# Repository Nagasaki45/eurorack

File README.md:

# Some eurorack modules

I'm trying. Let's see where it goes.

# Modules

- [1 2 3](<1 2 3/README.md>) - 8 steps resettable sequencial clock
- [I M smart](<I M smart/README.md>) - Utility mixer with some nice extras
- [let's play together](<lets play together/README.md>) - Analog + MIDI clock source

## Resources

- [Music Thing Modular parts library](https://github.com/TomWhitwell/MTM-Parts-Library).

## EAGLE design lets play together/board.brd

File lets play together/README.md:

# let's play together

## Analog + MIDI clock source in 4 hp

A clock module to sync your eurorack and external MIDI gear. The analog clock at the `CLK` output always ticks and the MIDI clock has a switch to start and stop that send the appropriate MIDI messages when flicked either side. There's a jumper at the back to send the analog clock to the gate bus, if you want to minimise cables to your other clocked modules.

### Summary of features

- Analog + MIDI clock
- MIDI start and stop toggle
- Can be set to output analog clock to gate bus via jumper
- Arduino based, so can be hacked (to change analog PPQN, tempo range, start and stop toggle functionality, etc.)
- MIDI clock output switchable between MIDI TRS type A and type B at with a switch at the back

## Specs

- Width: 4hp
- Depth: 29mm
- Power: 29mA @ 12V / <1mA @ -12V

## Build notes

- The LED orientation is not marked on the PCB. The longer (positive) leg should be closer to the edge of the board.
- I use an unbranded arduino pro mini 5V 16MHz ATMega328. A pro micro should also work. It's slightly more expensive, but is simpler to work with due to onboard USB connection.
- The arduino sketch depends on the [midilab's uClock](https://github.com/midilab/uClock) library. Make sure to install it first.

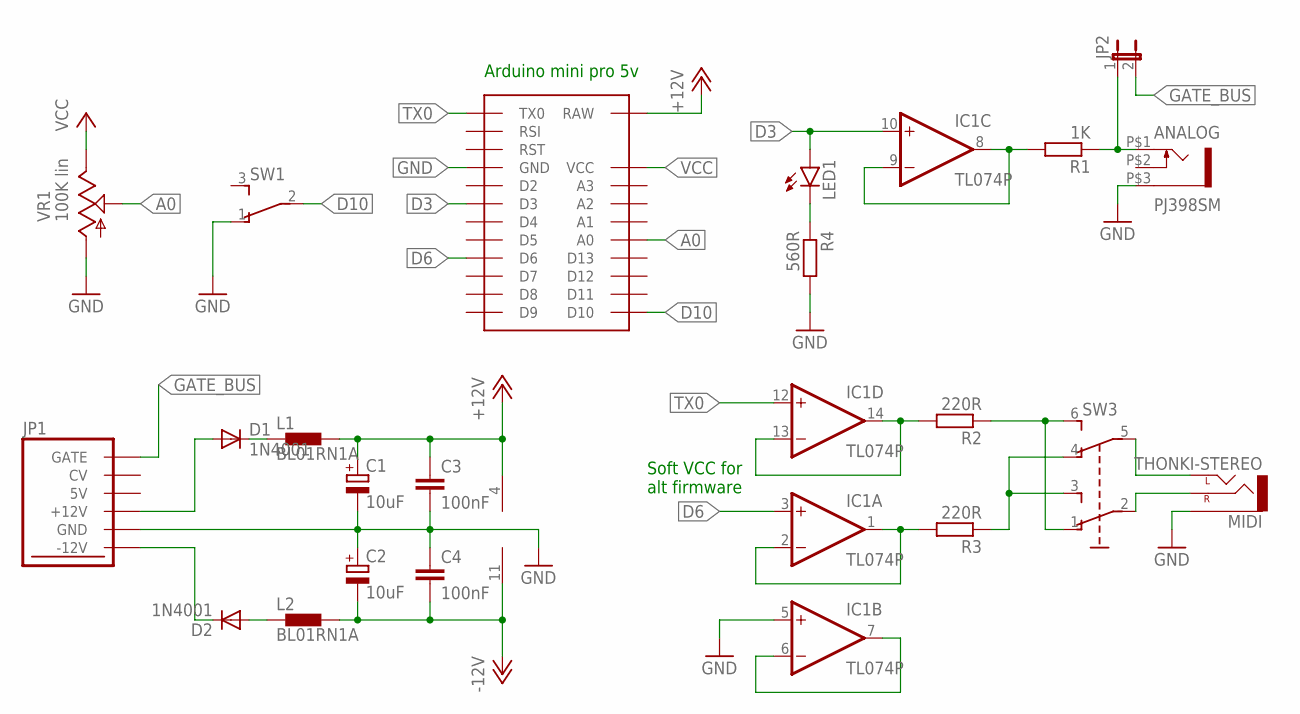
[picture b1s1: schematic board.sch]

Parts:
ANALOG: PJ398SM; WQP-PJ301M-12_JACK
C1, C2: 10uF; E2,5-6E; MPN UVR2A100MED1TD
C3, C4: 100nF; C025-024X044; MPN MC0805Y104M500A2.54MM
D1, D2: 1N4001; DO41-10; MPN 1N4001-E3/54
IC1: TL074P; DIL14; MPN TL074BCN
JP1: EUROPOWER16
JP2: JP1E; JP1; MPN 826926-2
JP3: ARDUINO_PRO_MINI_SOCKET
L1, L2: BL01RN1A; MPN BL01RN1A1D2B
LED1: LED3MM; MPN HLMP-1700
MIDI: THONKI-STEREO; WQP-PJ366ST_JACK
R1: 1K; 0204/5; MPN LR0204F1K0
R2, R3: 220R; 0204/5; MPN LR0204F100K
R4: 560R; 0204/5; MPN LR0204F100K
SW1: SUB-MINI; TL3XPO
SW3: JS202011CQN; MPN JS202011CQN
VR1: 100K lin; 9MM_SNAP-IN_POT

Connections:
+12V: C1.+, C3.1, IC1.4 (V+), JP3.1 (RAW), L1.2
-12V: C2.-, C4.2, IC1.11 (V-), L2.2
A0: JP3.8 (A0), VR1.2 (S)
CLOCK: ANALOG.P$1 (2), JP2.1, R1.1
D3: IC1.10 (+IN), JP3.18 (D3), LED1.A
D6: IC1.3 (+IN), JP3.21 (D6)
D10: JP3.12 (D10), SW1.2
GATE_BUS: JP1.15 (GATE), JP1.16 (GATE), JP2.2
GND: ANALOG.P$3 (1), C1.-, C2.+, C3.2, C4.1, IC1.5 (+IN), JP1.3 (GND), JP1.4 (GND), JP1.5 (GND), JP1.6 (GND), JP1.7 (GND), JP1.8 (GND), JP3.2 (GND), JP3.16 (GND), MIDI.P$3_SLEEVE (SLEEVE), R4.2, SW1.1 (O), VR1.1 (A)
unnamed: D1.A, JP1.9 (+12V), JP1.10 (+12V)
unnamed: D2.C, JP1.1 (-12V), JP1.2 (-12V)
unnamed: D1.C, L1.1
unnamed: D2.A, L2.1
unnamed: IC1.1 (OUT), IC1.2 (-IN), R3.2
unnamed: R2.1, SW3.1 (A1), SW3.6 (B2)
unnamed: IC1.13 (-IN), IC1.14 (OUT), R2.2
unnamed: LED1.K (C), R4.1
unnamed: MIDI.P$1_TIP (LEFT), SW3.5 (COM2)
unnamed: MIDI.P$2_SWITCH (RIGHT), SW3.2 (COM1)
unnamed: R3.1, SW3.3 (B1), SW3.4 (A2)
unnamed: IC1.6 (-IN), IC1.7 (OUT)
unnamed: IC1.8 (OUT), IC1.9 (-IN), R1.2
TX0: IC1.12 (+IN), JP3.13 (TX0)
VCC: JP3.4 (VCC), VR1.3 (E)

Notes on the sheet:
Arduino mini pro 5v
Soft VCC for alt firmware

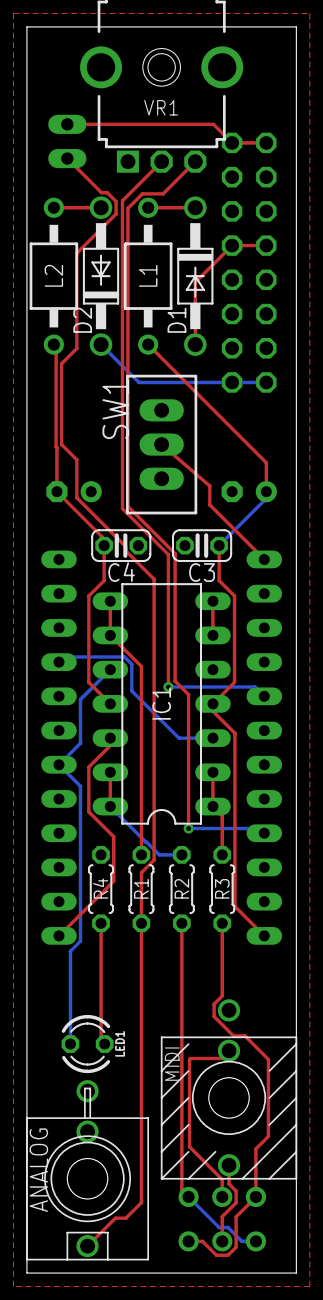
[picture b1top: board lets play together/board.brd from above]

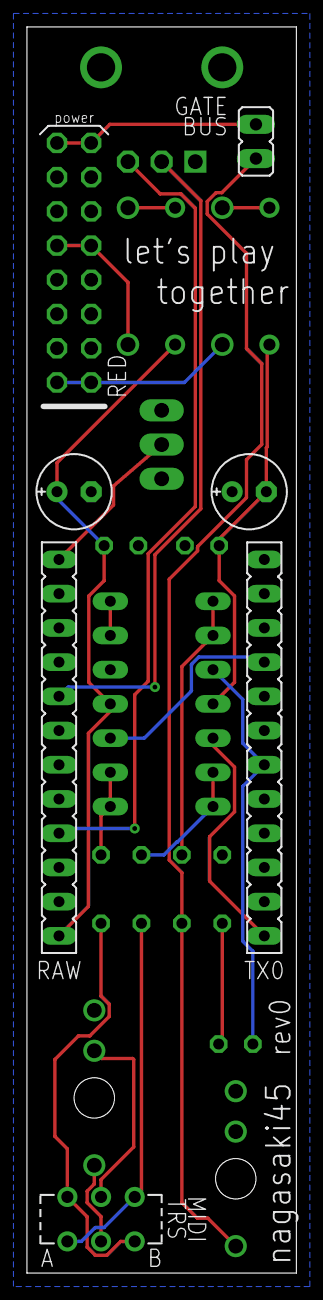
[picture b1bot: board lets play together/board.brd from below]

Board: 2 copper layers, 20.0 x 92.5 mm, 22 parts (6 on the bottom side), 24 nets.

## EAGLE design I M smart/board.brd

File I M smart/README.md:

# I M smart

## Utility mixer with some nice extras in 4 hp

At its basis this module is a 3 channels mixer, but with extra features down its sleeve! The first two channels have dedicated outputs. Connecting a patch cable to these outputs takes channel 1 or 2 out of the mix. Input 1 is normalised to ~+6 volts, so without anything plugged into input 1 the first knob can add positive voltages to the mix or to the dedicated output. Similarly, channel 2 is normalised to ~-6 volts, to add some negative voltages to the mix or to output 2. Channel 3's knob is an attenuverter. This channel is not normalised to anything, because normalised attenuverters are super annoying to set to 0. Lastly, there's only one PCB behind the panel, and a quite low components count, making it relatively cheap and easy build.

### Summary of features

- 3 channels mixer
- 2 attenuators
- 1 attenuverter
- Positive and negative manual voltages

## Specs

- Width: 4hp
- Depth: 25mm
- Power: 5mA @ 12V / 5mA @ -12V

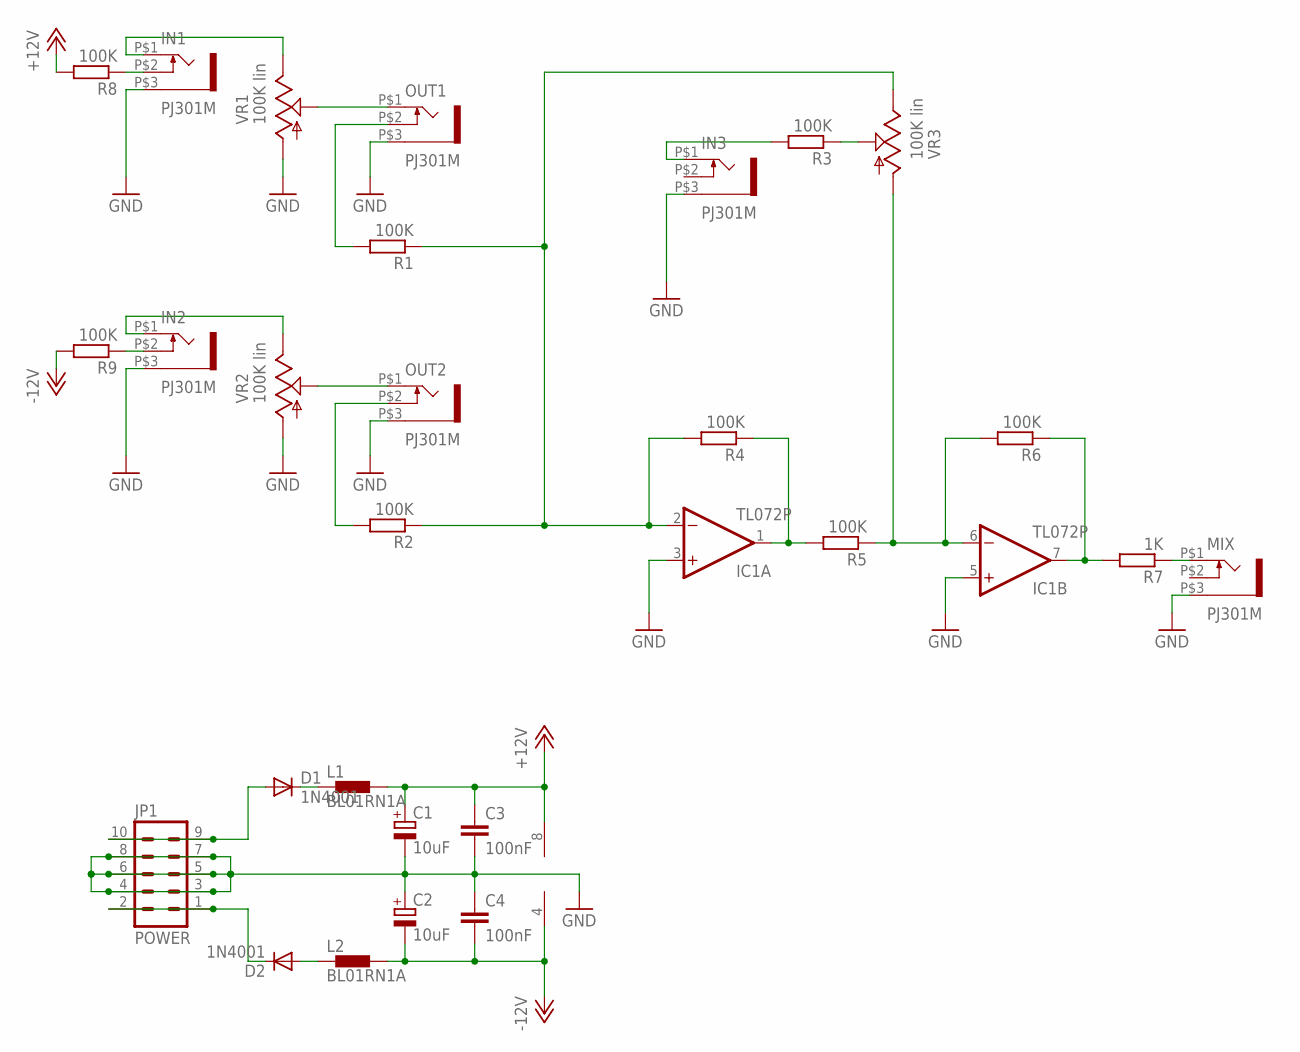
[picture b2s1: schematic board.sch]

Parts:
C1, C2: 10uF; E2,5-6E; MPN UVR2A100MED1TD
C3, C4: 100nF; C025-024X044; MPN MC0805Y104M500A2.54MM
D1, D2: 1N4001; DO41-10; MPN 1N4001-E3/54
IC1: TL072P; DIL08; MPN TL072IP
IN1, IN2, IN3: PJ301M; WQP-PJ301M-12_JACK
JP1: POWER; EURO_PWR_HEADER_FAT; MPN 2213S-10G
L1, L2: BL01RN1A; MPN BL01RN1A1D2B
MIX: PJ301M; WQP-PJ301M-12_JACK
OUT1, OUT2: PJ301M; WQP-PJ301M-12_JACK
R1, R2, R3, R4, R5, R6, R8, R9: 100K; 0204/5; MPN LR0204F100K
R7: 1K; 0204/5; MPN LR0204F1K0
VR1, VR2, VR3: 100K lin; 9MM_SNAP-IN_POT

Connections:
+12V: C1.+, C3.1, IC1.8 (V+), L1.2, R8.2
-12V: C2.-, C4.2, IC1.4 (V-), L2.2, R9.2
GND: C1.-, C2.+, C3.2, C4.1, IC1.3 (+IN), IC1.5 (+IN), IN1.P$3 (1), IN2.P$3 (1), IN3.P$3 (1), JP1.3, JP1.4, JP1.5, JP1.6, JP1.7, JP1.8, MIX.P$3 (1), OUT1.P$3 (1), OUT2.P$3 (1), VR1.1 (A), VR2.1 (A)
MIX+: MIX.P$1 (2), R7.1
MIXER: IC1.2 (-IN), R1.1, R2.1, R4.2, VR3.3 (E)
unnamed: D1.A, JP1.9, JP1.10
unnamed: D2.C, JP1.1, JP1.2
unnamed: D1.C, L1.1
unnamed: D2.A, L2.1
unnamed: IN1.P$1 (2), VR1.3 (E)
unnamed: IN2.P$1 (2), VR2.3 (E)
unnamed: OUT1.P$1 (2), VR1.2 (S)
unnamed: OUT2.P$1 (2), VR2.2 (S)
unnamed: IN3.P$1 (2), R3.2
unnamed: R3.1, VR3.2 (S)
unnamed: IN2.P$2 (3), R9.1
unnamed: IN1.P$2 (3), R8.1
unnamed: OUT1.P$2 (3), R1.2
unnamed: OUT2.P$2 (3), R2.2
unnamed: IC1.1 (OUT), R4.1, R5.2
unnamed: IC1.6 (-IN), R5.1, R6.2, VR3.1 (A)
unnamed: IC1.7 (OUT), R6.1, R7.2

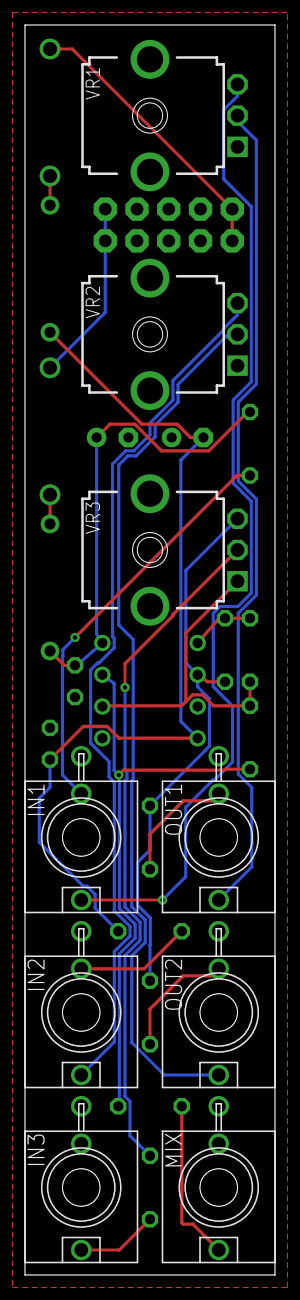
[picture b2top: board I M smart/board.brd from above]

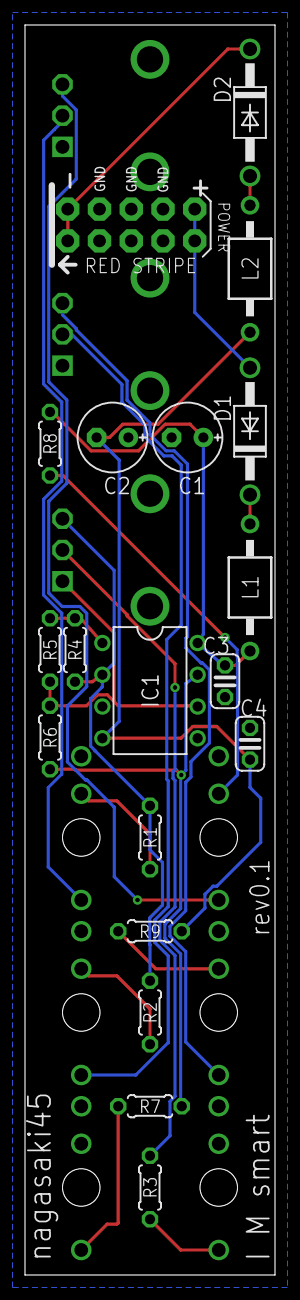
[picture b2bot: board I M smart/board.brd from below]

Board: 2 copper layers, 20.0 x 100.0 mm, 28 parts (19 on the bottom side), 22 nets.

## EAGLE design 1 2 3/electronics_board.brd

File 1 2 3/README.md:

# 1 2 3

## 8 steps resettable sequencial clock in 4 hp

With a clock going into the CLK input output 1 to 8 will go high one at a time. A reset input or a button can reset the sequence back to the 1st step. The outputs are designed to be mixed with simple passive multiples. No need for additional OR logic / gate combiner. For example, try to connect output 1 and 3 to a passive multiple or stackable and also to a kick drum trigger input, and output 5 and 8 in a similar fashion to a snare trigger input. Got the idea? The module can also work in audio rate to produce various sub-octaves and sync effects.

## Specs

- Width: 4hp
- Depth: 44mm
- Power: 29mA @ 12V / 16mA @ -12V

## Useful references

- [Ken Stone's gate sequencer](https://www.elby-designs.com/webtek/cgs/cgs89/cgs89_gate_sequencer.html)
- [Ken Stone's gate to trigger](https://www.muffwiggler.com/forum/viewtopic.php?t=46926)
- [Passive OR logic](https://forum.aemodular.com/thread/365/diy-project-02-passive-logic)
- [Non inverting transistor switch](http://www.timstinchcombe.co.uk/index.php?pge=a161)
- [4022 datasheet](https://www.ti.com/lit/ds/symlink/cd4022b.pdf)
- [Reset input simulation](http://www.falstad.com/circuit/circuitjs.html?cct=$+0+0.000005+0.9487735836358526+50+5+43%0Ar+96+240+96+288+0+100000%0Ar+240+240+240+288+0+100000%0Ag+240+304+240+320+0%0Ag+304+304+304+320+0%0AR+304+96+304+64+0+0+40+12+0+0+0.5%0At+272+224+304+224+0+1+-9.770126409985263+0.5279543655005605+100%0Ar+304+96+304+144+0+10000%0Ar+336+192+400+192+0+100000%0Ag+432+304+432+320+0%0AR+432+96+432+64+0+0+40+12+0+0+0.5%0Aw+304+192+336+192+0%0Aw+304+176+304+192+0%0Aw+304+208+304+192+0%0AO+464+160+496+160+0%0Aw+432+160+464+160+0%0At+400+192+432+192+0+1+0.5312969859863312+0.6035068512629786+100%0Ar+432+96+432+144+0+10000%0Aw+432+144+432+160+0%0Aw+432+160+432+176+0%0Ad+160+288+160+240+2+default%0Ac+112+224+144+224+0+1e-8+-0.5880744193515561%0Ag+160+304+160+320+0%0Ag+96+304+96+320+0%0Aw+304+240+304+304+0%0Aw+432+208+432+304+0%0Aw+240+288+240+304+0%0Aw+96+288+96+304+0%0Aw+96+224+96+240+0%0Aw+96+224+112+224+0%0Aw+144+224+160+224+0%0Aw+224+224+240+224+0%0Aw+240+224+272+224+0%0Aw+304+144+304+176+0%0AR+96+224+96+176+0+2+1000+3+3+0+0.5%0Aw+160+288+160+304+0%0Aw+240+224+240+240+0%0Aw+160+224+160+240+0%0Ar+176+224+224+224+0+10000%0Aw+160+224+176+224+0%0Ao+13+1+0+4098+20+0.1+0+1%0A)
- [LED calculator](http://ledcalc.com/)

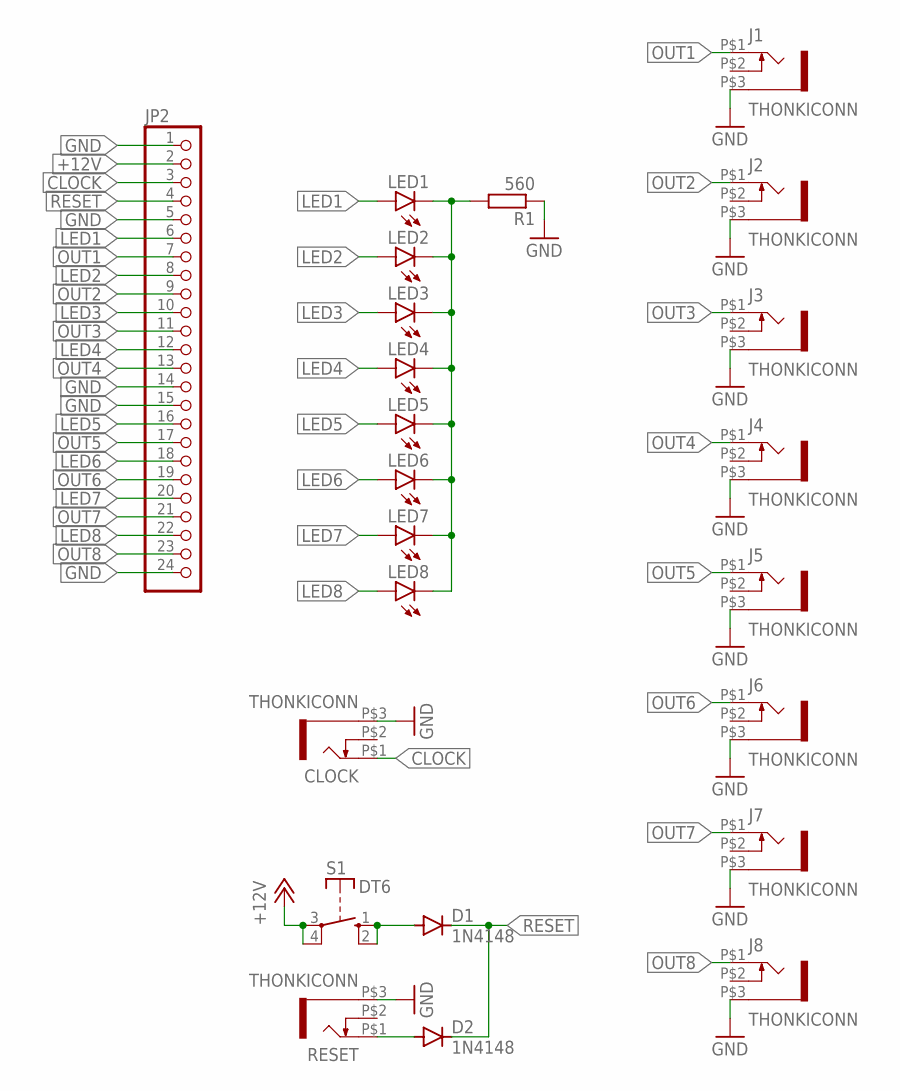
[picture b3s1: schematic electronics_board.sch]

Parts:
CLOCK: THONKICONN; WQP-PJ301M-12_JACK
D1, D2: 1N4148; DO35-7
J1, J2, J3, J4, J5, J6, J7, J8: THONKICONN; WQP-PJ301M-12_JACK
JP2: PINHD-1X24; 1X24
LED1, LED2, LED3, LED4, LED5, LED6, LED7, LED8: LED; LED_3MM; MPN HLMP-1700
R1: 560; 0204/5; MPN MCF 0.25W 560R
RESET: THONKICONN; WQP-PJ301M-12_JACK
S1: DT6

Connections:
+12V: JP2.2, S1.3, S1.4
CLOCK: CLOCK.P$1 (2), JP2.3
GND: CLOCK.P$3 (1), J1.P$3 (1), J2.P$3 (1), J3.P$3 (1), J4.P$3 (1), J5.P$3 (1), J6.P$3 (1), J7.P$3 (1), J8.P$3 (1), JP2.1, JP2.5, JP2.14, JP2.15, JP2.24, R1.1, RESET.P$3 (1)
LED1: JP2.6, LED1.A
LED2: JP2.8, LED2.A
LED3: JP2.10, LED3.A
LED4: JP2.12, LED4.A
LED5: JP2.16, LED5.A
LED6: JP2.18, LED6.A
LED7: JP2.20, LED7.A
LED8: JP2.22, LED8.A
unnamed: LED1.K (C), LED2.K (C), LED3.K (C), LED4.K (C), LED5.K (C), LED6.K (C), LED7.K (C), LED8.K (C), R1.2
unnamed: D1.A, S1.1 (S), S1.2 (S)
unnamed: D2.A, RESET.P$1 (2)
OUT1: J1.P$1 (2), JP2.7
OUT2: J2.P$1 (2), JP2.9
OUT3: J3.P$1 (2), JP2.11
OUT4: J4.P$1 (2), JP2.13
OUT5: J5.P$1 (2), JP2.17
OUT6: J6.P$1 (2), JP2.19
OUT7: J7.P$1 (2), JP2.21
OUT8: J8.P$1 (2), JP2.23
RESET: D1.C, D2.C, JP2.4

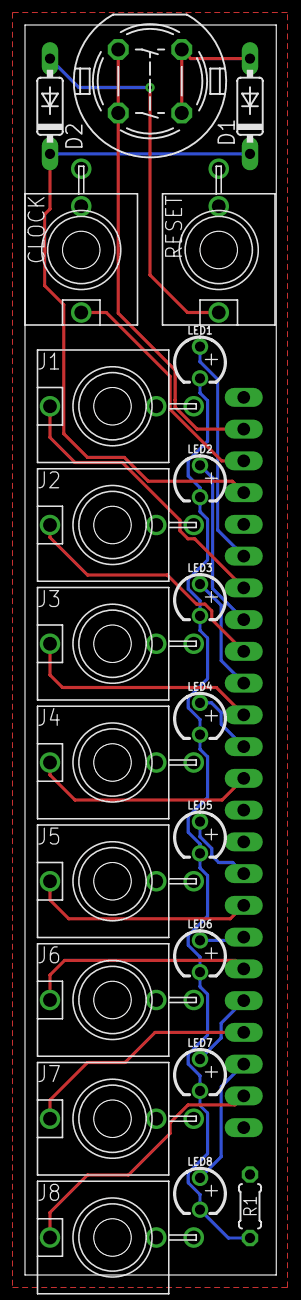
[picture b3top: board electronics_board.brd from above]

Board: 2 copper layers, 20.1 x 100.0 mm, 23 parts (1 on the bottom side), 23 nets.

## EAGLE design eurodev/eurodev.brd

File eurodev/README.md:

# eurodev

Breadboard developer tool for eurorack. Similar to [Transient Modules – Breadboard Supply](https://www.thonk.co.uk/shop/transient-breadboard-kit/). Practicing my Eagle skills :-)

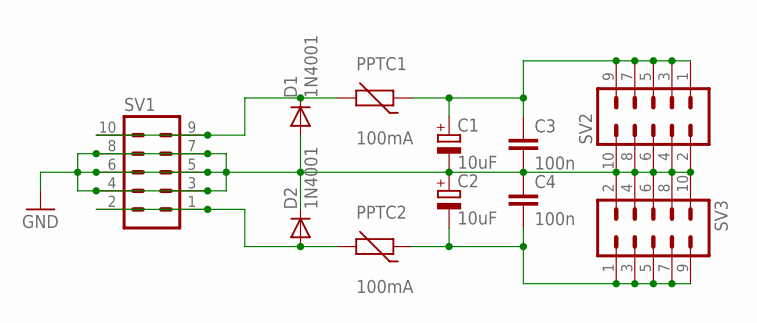
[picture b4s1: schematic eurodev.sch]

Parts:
C1, C2: 10uF; E2,5-6E; MPN 35ZLG10MEFC5X7
C3, C4: 100n; C050-025X075; MPN B32529C0104J289
D1, D2: 1N4001; DO41-10; MPN 1N4001-E3/54
PPTC1, PPTC2: 100mA; R-5; MPN 60R010XU
SV1: 10_PIN_HEADER; MA05-2; MPN 67997-410HLF
SV2, SV3: MA05-2; MPN 67997-410HLF

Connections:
GND: C1.-, C2.+, C3.2, C4.1, D1.A, D2.C, SV1.3, SV1.4, SV1.5, SV1.6, SV1.7, SV1.8, SV2.2, SV2.4, SV2.6, SV2.8, SV2.10, SV3.2, SV3.4, SV3.6, SV3.8, SV3.10
unnamed: C1.+, C3.1, PPTC1.1, SV2.1, SV2.3, SV2.5, SV2.7, SV2.9
unnamed: C2.-, C4.2, PPTC2.1, SV3.1, SV3.3, SV3.5, SV3.7, SV3.9
unnamed: D1.C, PPTC1.2, SV1.9, SV1.10
unnamed: D2.A, PPTC2.2, SV1.1, SV1.2

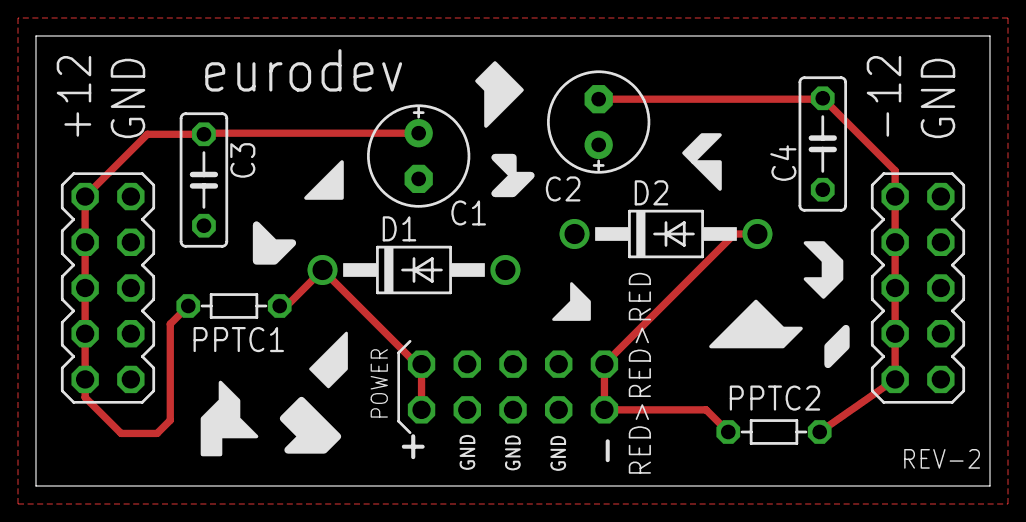
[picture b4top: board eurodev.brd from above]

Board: 2 copper layers, 53.0 x 25.0 mm, 11 parts (0 on the bottom side), 5 nets.

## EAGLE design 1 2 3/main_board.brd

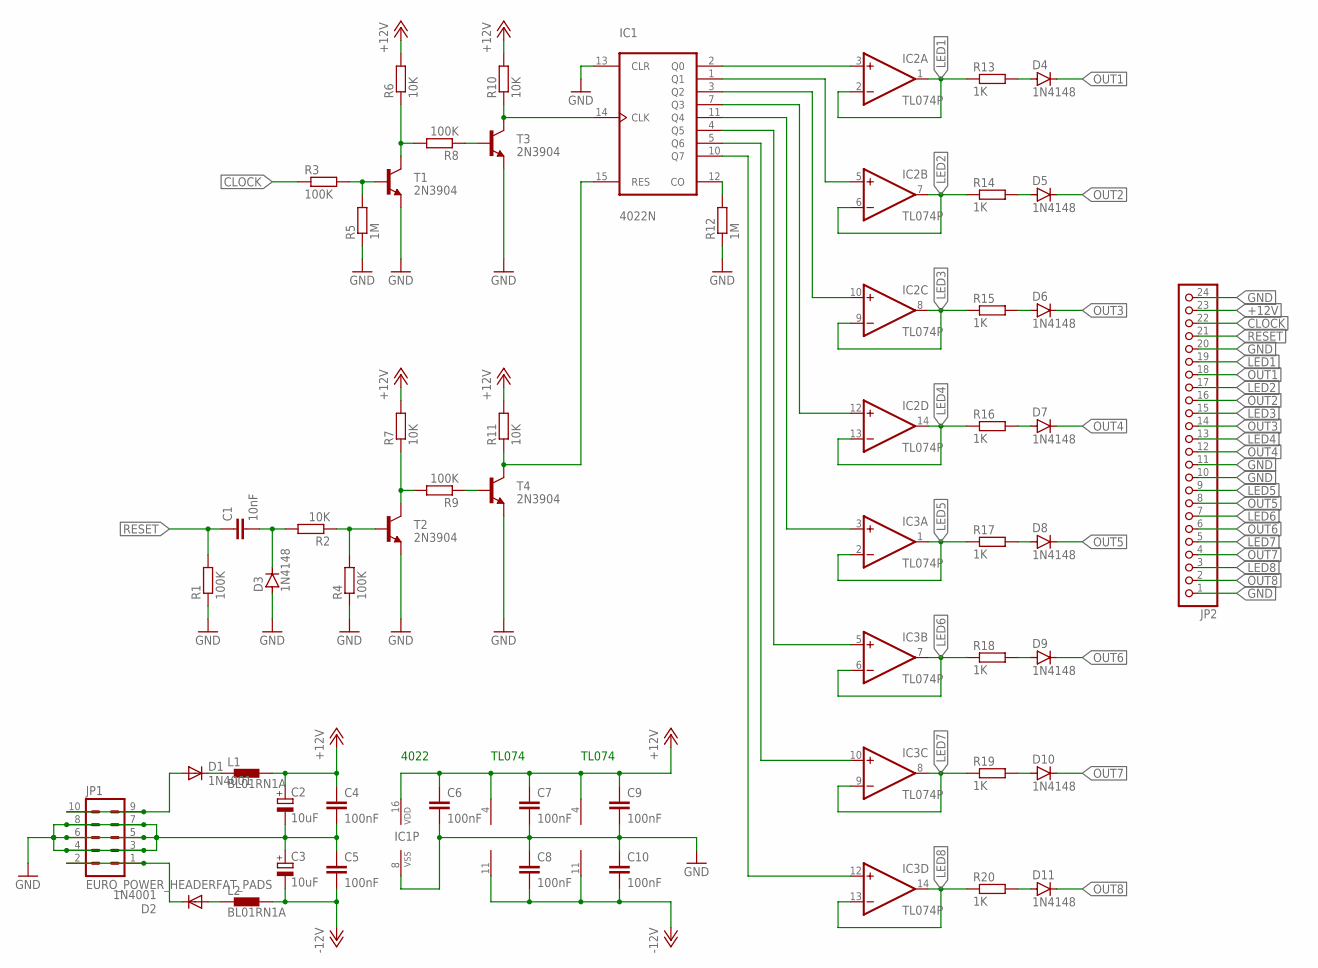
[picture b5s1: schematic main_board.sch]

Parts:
C1: 10nF; C025-024X044; MPN MC0805Y103M500A2.54MM
C2, C3: 10uF; E2,5-6E; MPN 35ZLG10MEFC5X7
C4, C5, C6, C7, C8, C9, C10: 100nF; C025-024X044; MPN B32529C0104J289
D1, D2: 1N4001; DO41-10; MPN 1N4001-E3/54
D3, D4, D5, D6, D7, D8, D9, D10, D11: 1N4148; DO35-7; MPN 1N5817-T
IC1: 4022N; DIL16; MPN CD4022BE
IC2, IC3: TL074P; DIL14; MPN TL074ACN
JP1: EURO_POWER_HEADERFAT_PADS; EURO_PWR_HEADER_FAT
JP2: PINHD-1X24/90; 1X24/90
L1, L2: BL01RN1A
R1, R3, R4, R8, R9: 100K; 0204/5; MPN MCF 0.25W 100K
R2, R6, R7, R10, R11: 10K; 0204/5; MPN MCF 0.25W 10K
R5, R12: 1M; 0204/5; MPN MCF 0.25W 1M
R13, R14, R15, R16, R17, R18, R19, R20: 1K; 0204/5; MPN MCF 0.25W 1K
T1, T2, T3, T4: 2N3904; TO92; MPN 2N3904

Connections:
+12V: C2.+, C4.1, C6.1, C7.1, C9.1, IC1.16 (VDD), IC2.4 (V+), IC3.4 (V+), JP2.23, L1.2, R6.2, R7.2, R10.2, R11.2
-12V: C3.-, C5.2, C8.2, C10.2, IC2.11 (V-), IC3.11 (V-), L2.2
CLOCK: JP2.22, R3.1
GND: C2.-, C3.+, C4.2, C5.1, C6.2, C7.2, C8.1, C9.2, C10.1, D3.A, IC1.8 (VSS), IC1.13 (CLR), JP1.3, JP1.4, JP1.5, JP1.6, JP1.7, JP1.8, JP2.1, JP2.10, JP2.11, JP2.20, JP2.24, R1.1, R4.1, R5.1, R12.1, T1.3 (E), T2.3 (E), T3.3 (E), T4.3 (E)
LED1: IC2.1 (OUT), IC2.2 (-IN), JP2.19, R13.1
LED2: IC2.6 (-IN), IC2.7 (OUT), JP2.17, R14.1
LED3: IC2.8 (OUT), IC2.9 (-IN), JP2.15, R15.1
LED4: IC2.13 (-IN), IC2.14 (OUT), JP2.13, R16.1
LED5: IC3.1 (OUT), IC3.2 (-IN), JP2.9, R17.1
LED6: IC3.6 (-IN), IC3.7 (OUT), JP2.7, R18.1
LED7: IC3.8 (OUT), IC3.9 (-IN), JP2.5, R19.1
LED8: IC3.13 (-IN), IC3.14 (OUT), JP2.3, R20.1
unnamed: D1.A, JP1.9, JP1.10
unnamed: D2.C, JP1.1, JP1.2
unnamed: D1.C, L1.1
unnamed: D2.A, L2.1
unnamed: D4.A, R13.2
unnamed: D5.A, R14.2
unnamed: D6.A, R15.2
unnamed: D7.A, R16.2
unnamed: IC1.2 (Q0), IC2.3 (+IN)
unnamed: IC1.1 (Q1), IC2.5 (+IN)
unnamed: IC1.3 (Q2), IC2.10 (+IN)
unnamed: IC1.7 (Q3), IC2.12 (+IN)
unnamed: IC1.11 (Q4), IC3.3 (+IN)
unnamed: IC1.4 (Q5), IC3.5 (+IN)
unnamed: IC1.5 (Q6), IC3.10 (+IN)
unnamed: IC1.10 (Q7), IC3.12 (+IN)
unnamed: R3.2, R5.2, T1.2 (B)
unnamed: C1.2, D3.C, R2.2
unnamed: R2.1, R4.2, T2.2 (B)
unnamed: R6.1, R8.2, T1.1 (C)
unnamed: IC1.12 (CO), R12.2
unnamed: D8.A, R17.2
unnamed: D9.A, R18.2
unnamed: D10.A, R19.2
unnamed: D11.A, R20.2
unnamed: R8.1, T3.2 (B)
unnamed: IC1.14 (CLK), R10.1, T3.1 (C)
unnamed: R7.1, R9.2, T2.1 (C)
unnamed: R9.1, T4.2 (B)
unnamed: IC1.15 (RES), R11.1, T4.1 (C)
OUT1: D4.C, JP2.18
OUT2: D5.C, JP2.16
OUT3: D6.C, JP2.14
OUT4: D7.C, JP2.12
OUT5: D8.C, JP2.8
OUT6: D9.C, JP2.6
OUT7: D10.C, JP2.4
OUT8: D11.C, JP2.2
RESET: C1.1, JP2.21, R1.2

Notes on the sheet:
TL074
4022

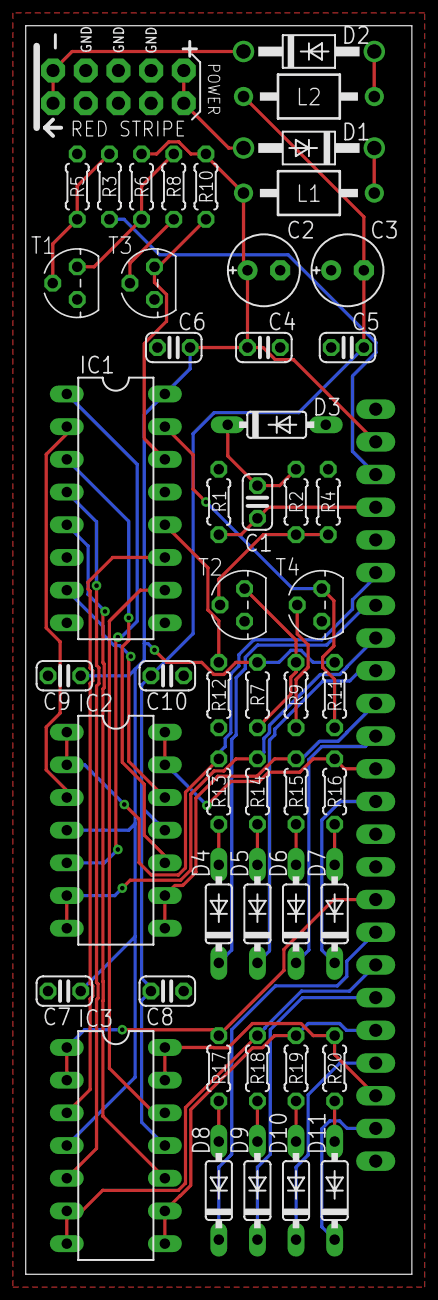
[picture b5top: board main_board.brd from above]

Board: 2 copper layers, 30.0 x 97.0 mm, 52 parts (1 on the bottom side), 51 nets.

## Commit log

2020-07-23 Add README and .gitignore
2020-07-23 Projects READMEs
2020-07-23 Correct projects' READMEs
2020-07-23 Script to generate eagle descriptions (html) from README.md
2020-07-30 Add BOM to 1 2 3 and I M smart
2020-07-30 Remove old panel render
2020-07-30 Improve I M smart README
2020-08-07 Don't connect the power rails directly to output as it shorts the entire case if connected to GND!
    Update I M smart to rev0.1. Compatible with panel.
2020-08-09 Add pics of modules. Fix #3
2020-08-09 Improve 1 2 3 subtitle
2020-08-10 Add eurotest
2020-08-10 Add specs (power & depth). Fix #1
2020-08-13 Add descriptions to the modules. Fix #2
2020-12-19 First lets play together attempt
2021-01-05 Let's play together rev0
2021-01-09 Remove eurotest, it's crap
2021-01-09 Drop DESCRIPTIONs, all info in READMEs
2021-01-09 Better READMEs and pics
2021-01-09 let's play together: Note about LED orientation in README
2021-01-09 Dropped descriptions and forgot to remove generate_descriptions.py. Doing so now
2021-01-15 lets play together: notes about arduino in README

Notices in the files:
parts and their libraries:
switch-ck: Creative Commons Attribution-ShareAlike 4.0 International
